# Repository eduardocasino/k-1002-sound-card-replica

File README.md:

# K-1002 8 bit audio Digital to Analog Converter replica

## About

This is a faithful replica of the K‑1002 8‑bit audio Digital‑to‑Analog Converter card for the KIM‑1, SYM‑1, and AIM‑65 computers, originally designed by MTU in the late ’70s.

I'm using the original K‑1002 documentation and high‑resolution photos from [Hans Otten's Retro Computing website](http://retro.hansotten.nl/).

### Important!

Although the card uses the familiar 44‑pin edge connector, it’s not a 1‑to‑1 match for the KIM‑1 application bus, so an adapter is required, as explained in the manual. I’ve also designed such an adapter, which you can find in the `adapter` folder.

## Building

There’s nothing particularly special about assembling the board. As with any other PCB, just start soldering components in order of height. All the ICs are socketed.

There’s a BOM spreadsheet in the `card/docs` folder, but there are a few things to keep in mind regarding some of the components:

* R1 to R13 are 51K resistors that need to be matched within 1%. You can either use modern metal‑film resistors with that tolerance or manually match carbon ones. I went with the latter to keep the look closer to the original.
Also, the documentation isn’t very clear about whether &plusmn;1% is actually enough or if it really means &plusmn;0.5% (so that all resistors fall within a 1% spread). I chose the latter interpretation as well.

* The 92PU01 and 92PU51 transistors are no longer available. The BD135‑10 and BD136‑10 are perfectly good functional replacements, but they use a different package and footprint, so you’ll need to bend the leads to fit them on the board.
 **NOTE**: They *must* be the "-10" variants!!

* The original potentiometer is no longer manufactured. A drop‑in replacement is the Piher PT15NH06 with the adjustment wheel. **NOTE**: Make sure you get the NH06 variant.

* The Keystone 571 RCA connector is no longer manufactured. Some suppliers may still have remaining stock, such as [TME](https://tme.eu) in Europe.

## KIM-1 Software and PC Utilities

I've only built it on a Debian Linux and on WSL with Ubuntu. I can't give support for other systems, sorry.

### Prerequisites

Any modern Linux distribution, tested on `Debian 12.6` and `Ubuntu 24.04`

Install the required packages:

```console
$ sudo apt update
$ sudo apt install build-essential cc65
```

### Build and usage

Just go to the `software` folder and run`make`:

```console
$ cd software
$ make
```

This will build the PC utilities and the KIM‑1 demo programs. The latter are generated in PAP format and are named with a numeric prefix that matches the file numbers in the K‑1002‑1L 8‑BIT Digital Music Software manual. Use them as instructed there.

Additionally, pcmplay.pap is a simple PCM player that plays a short sound snippet. Load it into your KIM-1 and run it at `$0200`.

The PC utilities are built into `software/utils/bin`:

* `wavegen` is a modern C version of the `kimfs` program. It generates a waveform table suitable for use with the MTU utilities from a very simle YAML description file.

* `notcmp` is the C version of the NOTRAN compiler. It accepts the same input files as its MTU counterpart and generates compatible object code for the NOTRAN interpreter.

* `notint` is a NOTRAN interpreter simulator that can either play a NOTRAN bytecode file through an ALSA device or generates WAV files to be played with any WAV player.

Run any of them without arguments to see the usage instructions.

## Licensing

This is a personal project that I am sharing in case it is of interest to any retrocomputing enthusiast and all the information in this repository is provided "as is", without warranty of any kind. I am not liable for any damages that may occur, whether it be to individuals, objects, KIM-1 computers, kittens or any other pets. **It should also be noted that everything in this repository is a work in progress and, although the board has been tested, may contain errors. Therefore, anyone who chooses to use it does so at their own risk**.

### Card

Th K-1002 replica is licensed under a [Creative Commons Attribution-NonCommercial 4.0 International License](http://creativecommons.org/licenses/by-nc/4.0/).

### Adapter

The adapter card is licensed under a [Creative Commons Attribution-ShareAlike 4.0 International License](http://creativecommons.org/licenses/by-sa/4.0/).

### MTU Software

Although it probably doesn’t matter much nowadays, since this software was written for a very obsolete and rare piece of hardware, the material is still copyrighted by MICRO TECHNOLOGY UNLIMITED, a company that is [still in business](http://www.mtu.com/catalog/index.php). I’m sharing it here solely to help anyone who owns a K‑1002 card.

### PC Utilities

All my code is licensed under the GNU General Public License, Version 3.

## Acknowledgements

* Hans Otten and his [Retro Computing blog](http://retro.hansotten.nl/). A lot of information and high resolution pictures of a K-1002

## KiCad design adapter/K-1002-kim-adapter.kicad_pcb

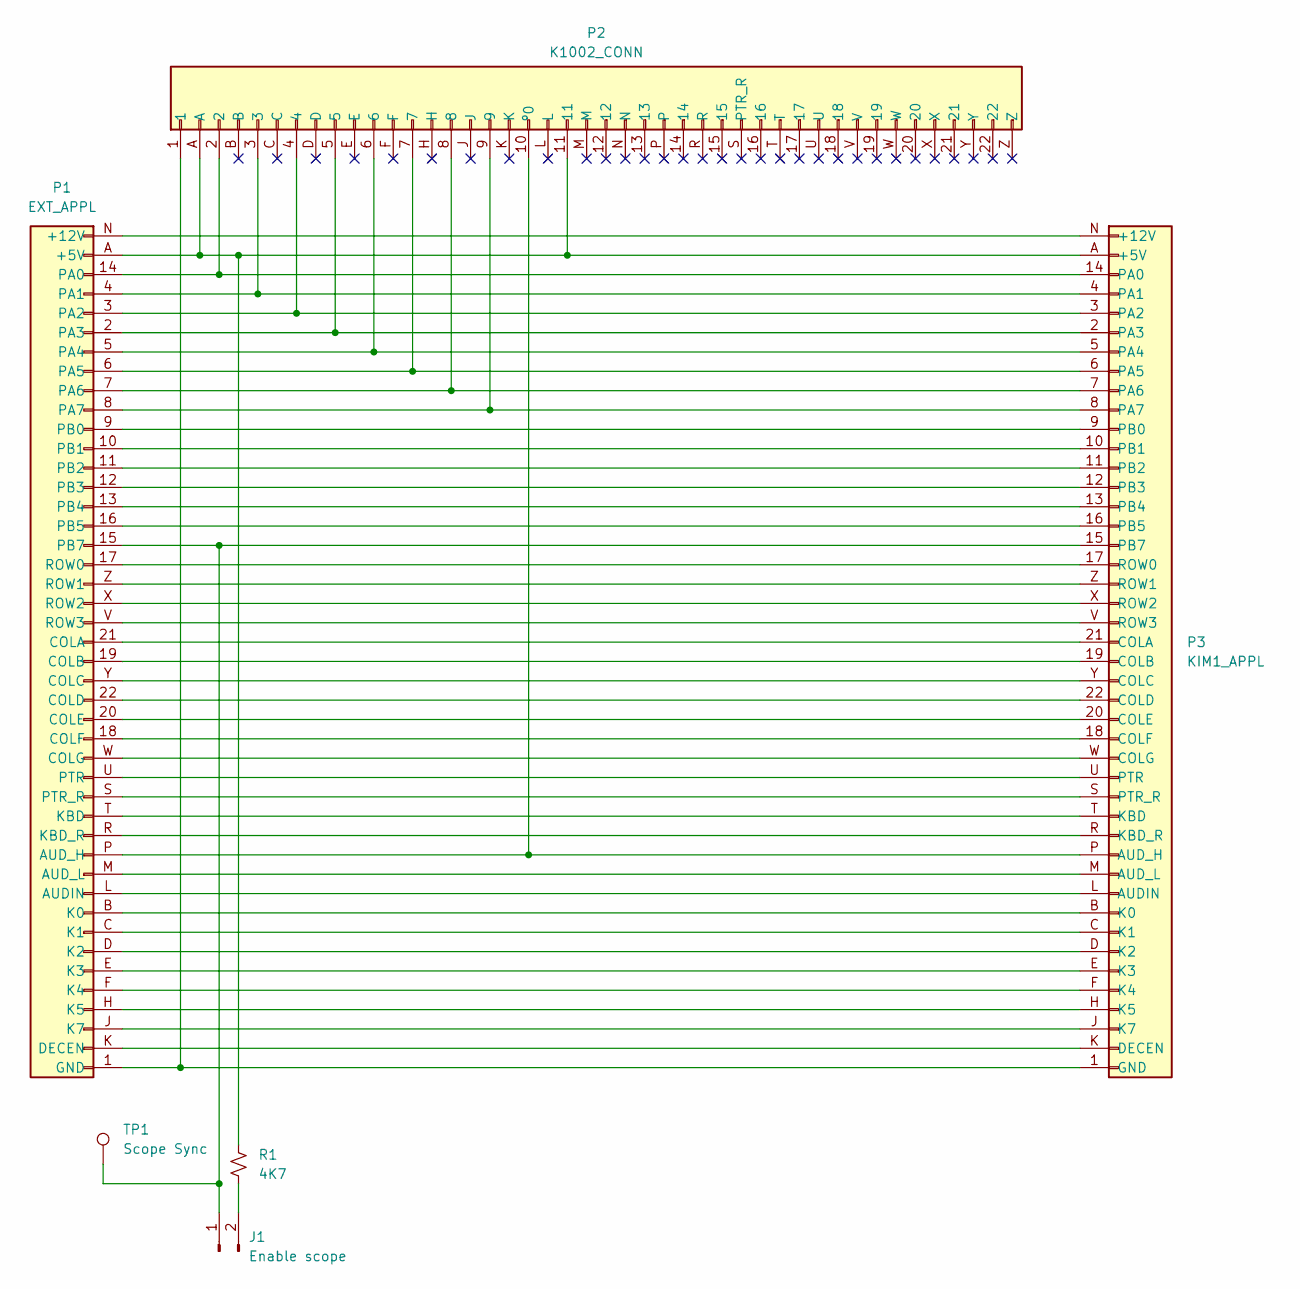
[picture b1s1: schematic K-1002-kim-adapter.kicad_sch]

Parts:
J1: Enable scope; PinHeader_1x02_P2.54mm_Vertical
P1: EXT_APPL; KIM_EDGE
P2: K1002_CONN; EDAC-3.96-2x22
P3: KIM1_APPL; APPL_CONN
R1: 4K7; R_Axial_DIN0207_L6.3mm_D2.5mm_P7.62mm_Horizontal
TP1: Scope Sync; TestPoint_3.0

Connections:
unnamed: J1.1, P1.15 (PB7), P3.15 (PB7), TP1.1
unnamed: J1.2, R1.2
unnamed: P1.A (+5V), P2.11, P2.A, P3.A (+5V), R1.1
unnamed: P1.N (+12V), P3.N (+12V)
unnamed: P1.L (AUDIN), P3.L (AUDIN)
unnamed: P1.P (AUD_H), P2.10 (º0), P3.P (AUD_H)
unnamed: P1.M (AUD_L), P3.M (AUD_L)
unnamed: P1.21 (COLA), P3.21 (COLA)
unnamed: P1.19 (COLB), P3.19 (COLB)
unnamed: P1.Y (COLC), P3.Y (COLC)
unnamed: P1.22 (COLD), P3.22 (COLD)
unnamed: P1.20 (COLE), P3.20 (COLE)
unnamed: P1.18 (COLF), P3.18 (COLF)
unnamed: P1.W (COLG), P3.W (COLG)
unnamed: P1.K (DECEN), P3.K (DECEN)
unnamed: P1.1 (GND), P2.1, P3.1 (GND)
unnamed: P1.B (K0), P3.B (K0)
unnamed: P1.C (K1), P3.C (K1)
unnamed: P1.D (K2), P3.D (K2)
unnamed: P1.E (K3), P3.E (K3)
unnamed: P1.F (K4), P3.F (K4)
unnamed: P1.H (K5), P3.H (K5)
unnamed: P1.J (K7), P3.J (K7)
unnamed: P1.T (KBD), P3.T (KBD)
unnamed: P1.R (KBD_R), P3.R (KBD_R)
unnamed: P1.14 (PA0), P2.2, P3.14 (PA0)
unnamed: P1.4 (PA1), P2.3, P3.4 (PA1)
unnamed: P1.3 (PA2), P2.4, P3.3 (PA2)
unnamed: P1.2 (PA3), P2.5, P3.2 (PA3)
unnamed: P1.5 (PA4), P2.6, P3.5 (PA4)
unnamed: P1.6 (PA5), P2.7, P3.6 (PA5)
unnamed: P1.7 (PA6), P2.8, P3.7 (PA6)
unnamed: P1.8 (PA7), P2.9, P3.8 (PA7)
unnamed: P1.9 (PB0), P3.9 (PB0)
unnamed: P1.10 (PB1), P3.10 (PB1)
unnamed: P1.11 (PB2), P3.11 (PB2)
unnamed: P1.12 (PB3), P3.12 (PB3)
unnamed: P1.13 (PB4), P3.13 (PB4)
unnamed: P1.16 (PB5), P3.16 (PB5)
unnamed: P1.U (PTR), P3.U (PTR)
unnamed: P1.S (PTR_R), P3.S (PTR_R)
unnamed: P1.17 (ROW0), P3.17 (ROW0)
unnamed: P1.Z (ROW1), P3.Z (ROW1)
unnamed: P1.X (ROW2), P3.X (ROW2)
unnamed: P1.V (ROW3), P3.V (ROW3)

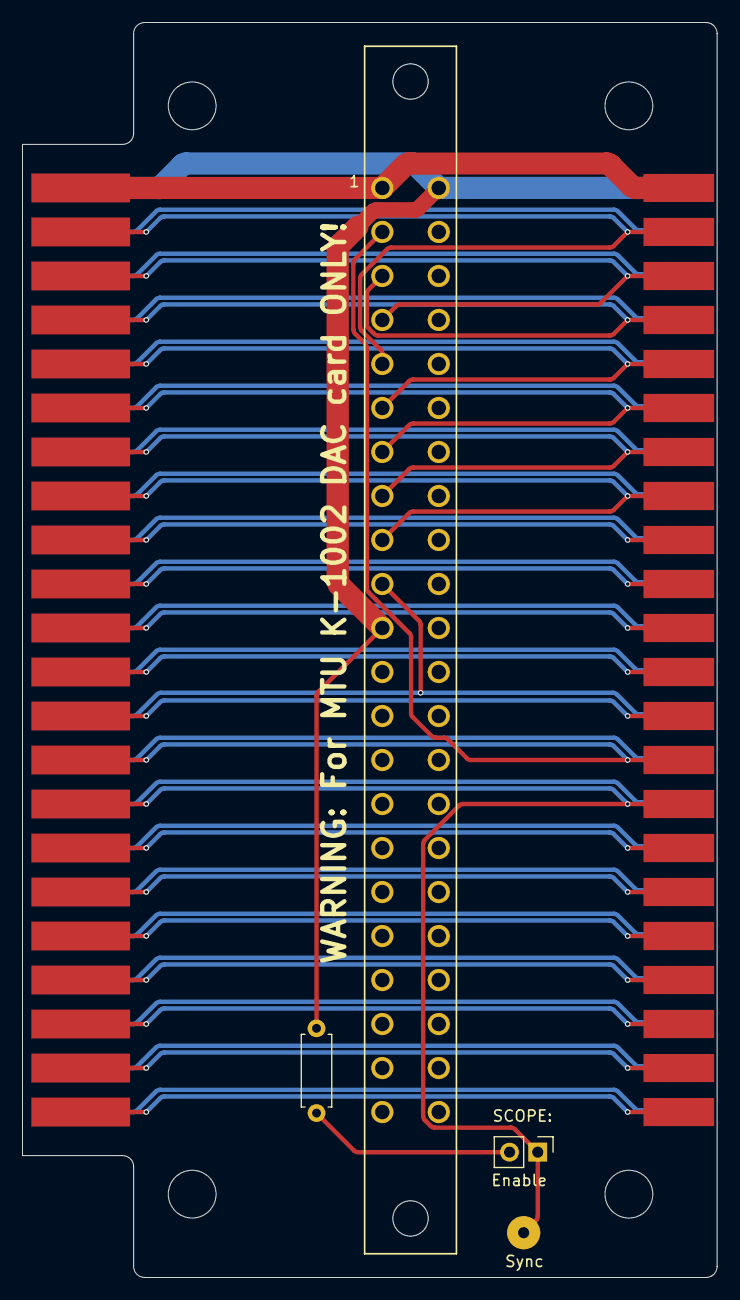
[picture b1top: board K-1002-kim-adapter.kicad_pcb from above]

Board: 2 copper layers, 62.5 x 112.9 mm, 10 parts (0 on the bottom side), 45 nets.

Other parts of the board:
M1, M1#2, M1#3, M2: MountingHole_4.3mm_M4

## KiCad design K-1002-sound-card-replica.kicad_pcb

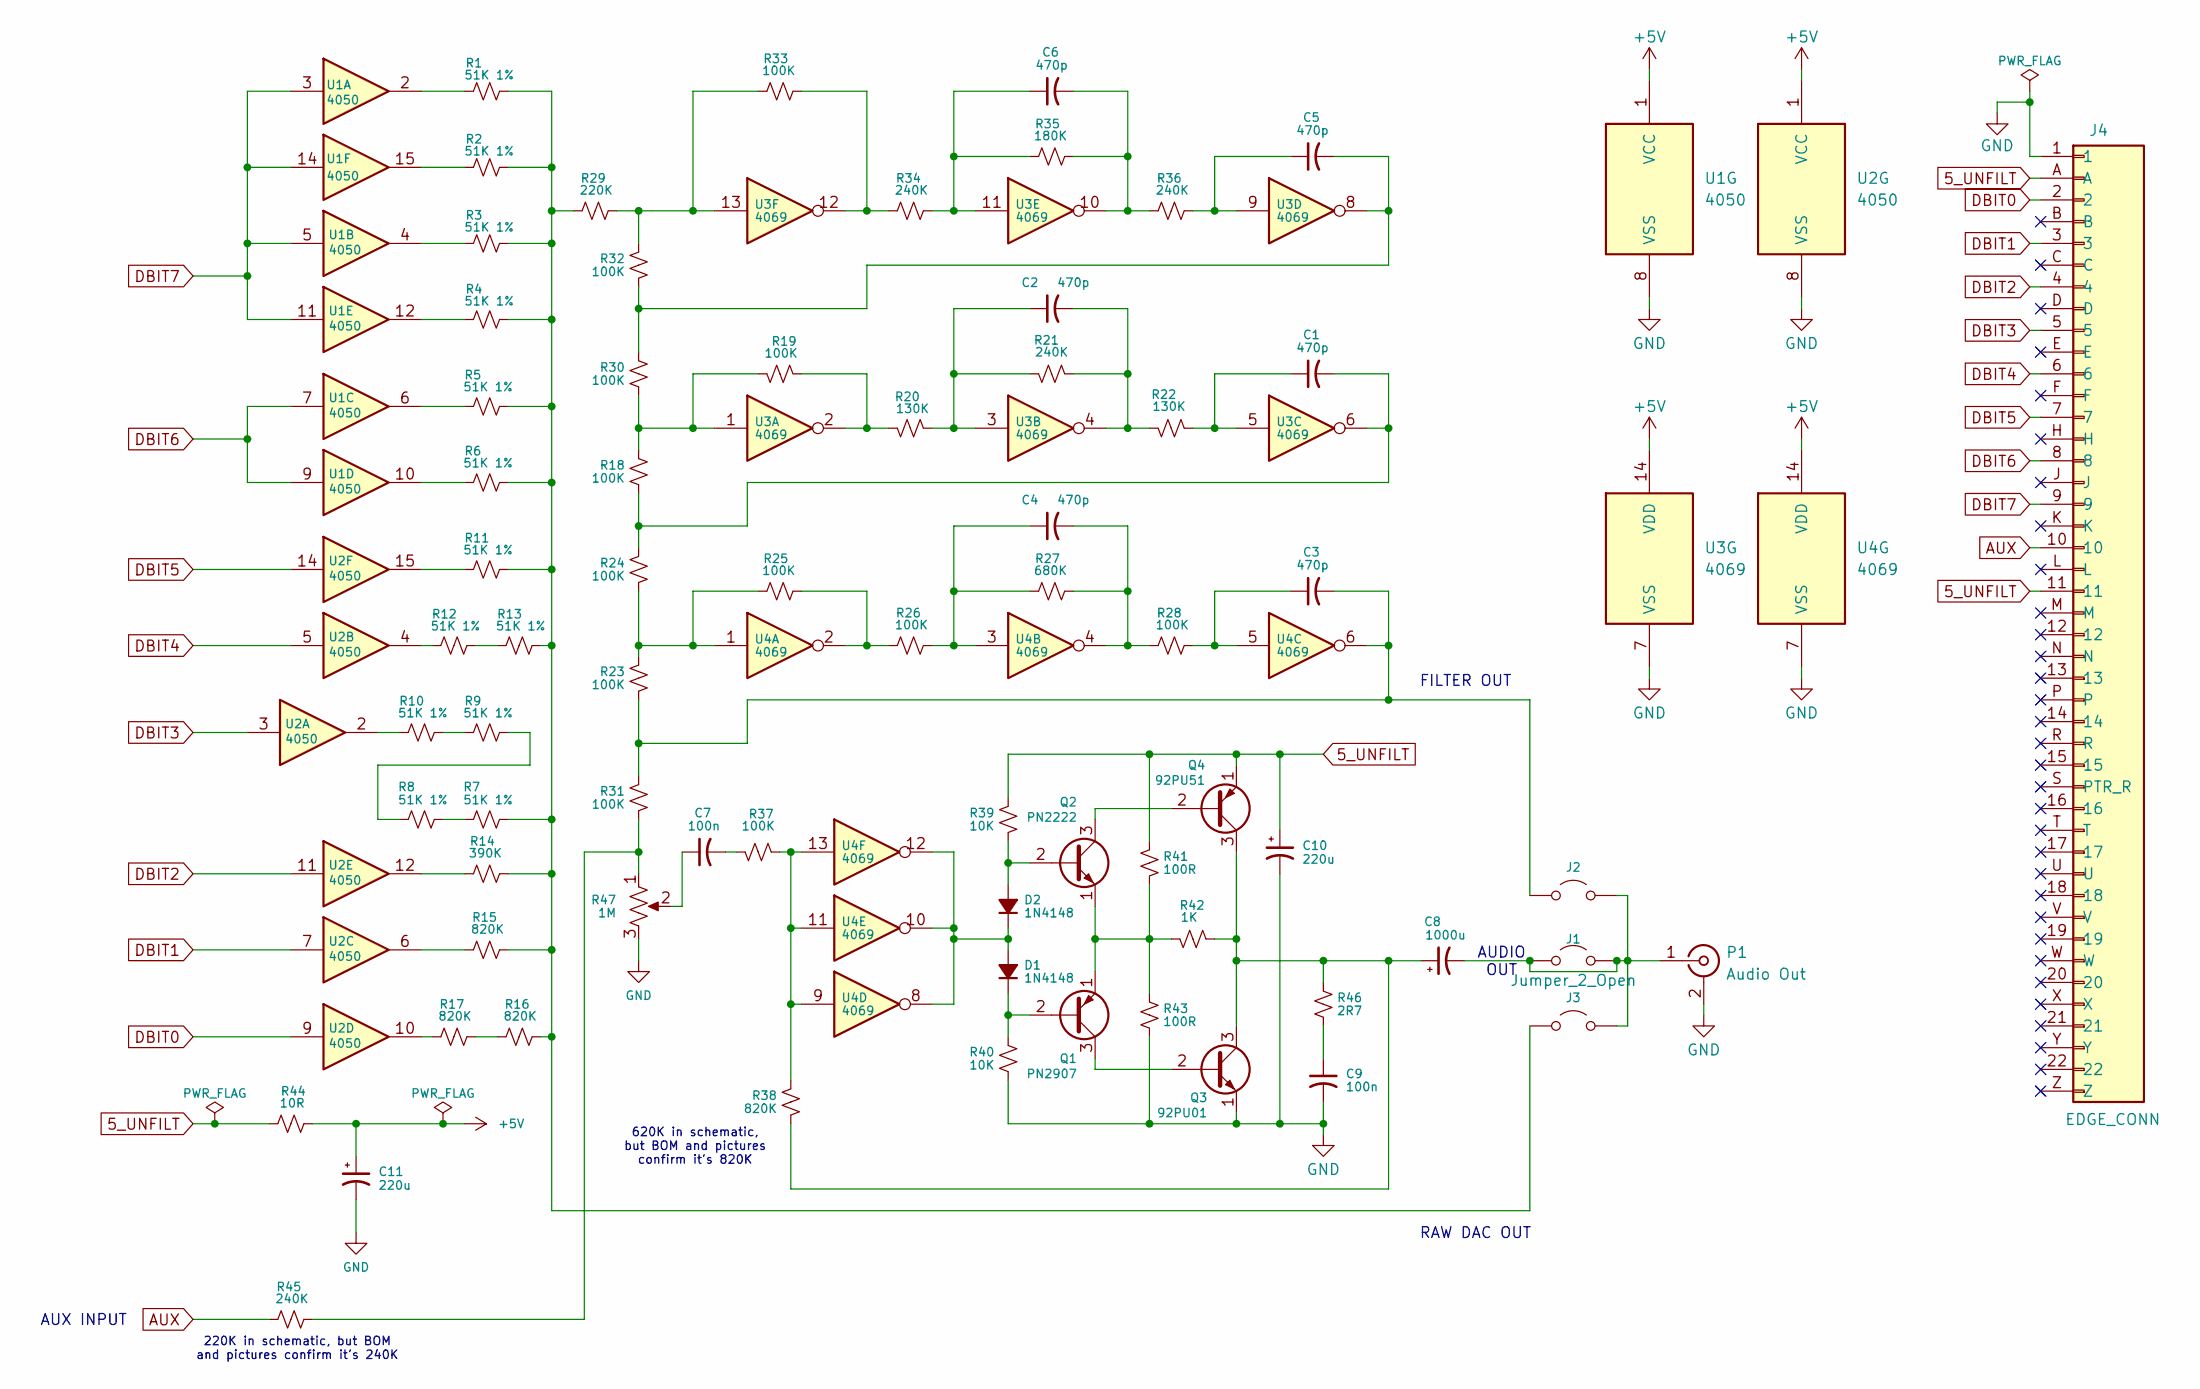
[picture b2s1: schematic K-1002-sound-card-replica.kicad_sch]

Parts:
C1, C2, C3, C4, C5, C6: 470p; C_Axial_L10.3mm_D4.7mm_P12.70mm_Horizontal
C7, C9: 100n; C_Disc_D7.0mm_W2.5mm_P6.35mm
C8: 1000u; C_Radial_D12.5mm_H20.0mm_P5.00mm
C10, C11: 220u; C_Radial_D10.0mm_H12.5mm_P5.00mm
D1, D2: 1N4148; D_DO-35_SOD27_P12.70mm_Horizontal
J1, J2, J3: Jumper_2_Open; Bridge_Open_P7.62mm
J4: EDGE_CONN
P1: Audio Out; Keystone_571_RCA
Q1: PN2907; TO-92-Custom
Q2: PN2222; TO-92-Custom
Q3: 92PU01; TO-92-Custom
Q4: 92PU51; TO-92-Custom
R1, R2, R3, R4, R5, R6, R7, R8, R9, R10, R11, R12, R13: 51K 1%; R_Axial_DIN0204_L3.6mm_D2.5mm_P12.70mm_Horizontal_51K
R14: 390K; R_Axial_DIN0204_L3.6mm_D2.5mm_P12.70mm_Horizontal_390K
R15, R16, R17, R38: 820K; R_Axial_DIN0204_L3.6mm_D2.5mm_P12.70mm_Horizontal_820K
R18, R19, R23, R24, R25, R26, R28, R30, R31, R32, R33, R37: 100K; R_Axial_DIN0204_L3.6mm_D2.5mm_P12.70mm_Horizontal_100K
R20, R22: 130K; R_Axial_DIN0204_L3.6mm_D2.5mm_P12.70mm_Horizontal_130K
R21, R34, R36, R45: 240K; R_Axial_DIN0204_L3.6mm_D2.5mm_P12.70mm_Horizontal_240K
R27: 680K; R_Axial_DIN0204_L3.6mm_D2.5mm_P12.70mm_Horizontal_680K
R29: 220K; R_Axial_DIN0204_L3.6mm_D2.5mm_P12.70mm_Horizontal_220K
R35: 180K; R_Axial_DIN0204_L3.6mm_D2.5mm_P12.70mm_Horizontal_180K
R39, R40: 10K; R_Axial_DIN0204_L3.6mm_D2.5mm_P12.70mm_Horizontal_10K
R41, R43: 100R; R_Axial_DIN0204_L3.6mm_D2.5mm_P12.70mm_Horizontal_100R
R42: 1K; R_Axial_DIN0204_L3.6mm_D2.5mm_P12.70mm_Horizontal_1K
R44: 10R; R_Axial_DIN0204_L3.6mm_D2.5mm_P12.70mm_Horizontal_10R
R46: 2R7; R_Axial_DIN0204_L3.6mm_D2.5mm_P12.70mm_Horizontal_2R7
R47: 1M; Piher_PT15-NH-06
U1, U2: 4050; DIP-16_W7.62mm_LongPads
U3, U4: 4069; DIP-14_W7.62mm_LongPads

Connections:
5_UNFILT: C10.1, J4.11, J4.A, Q4.1 (E), R39.1, R41.2, R44.1
+5V: C11.1, R44.2, U1.1 (VCC), U1.16, U2.1 (VCC), U2.16, U3.14 (VDD), U4.14 (VDD)
AUX: J4.10 (º0), R45.1
DBIT0: J4.2, U2.9
DBIT1: J4.3, U2.7
DBIT2: J4.4, U2.11
DBIT3: J4.5, U2.3
DBIT4: J4.6, U2.5
DBIT5: J4.7, U2.14
DBIT6: J4.8, U1.7, U1.9
DBIT7: J4.9, U1.3, U1.5, U1.11, U1.13, U1.14
GND: C9.2, C10.2, C11.2, J4.1, P1.2 (Ext), Q3.1 (E), R40.1, R43.2, R47.3, U1.8 (VSS), U2.8 (VSS), U3.7 (VSS), U4.7 (VSS)
unnamed: C1.1, R22.1, U3.5
unnamed: C1.2, R18.1, R24.1, U3.6
unnamed: C2.1, R20.1, R21.2, U3.3
unnamed: C2.2, R21.1, R22.2, U3.4
unnamed: C3.1, R28.2, U4.5
unnamed: C4.1, R26.2, R27.1, U4.3
unnamed: C4.2, R27.2, R28.1, U4.4
unnamed: C5.1, R36.2, U3.9
unnamed: C5.2, R30.2, R32.2, U3.8
unnamed: C6.1, R34.2, R35.1, U3.11
unnamed: C6.2, R35.2, R36.1, U3.10
unnamed: C7.1, R47.2
unnamed: C7.2, R37.2
unnamed: C9.1, R46.2
unnamed: D1.2 (A), D2.1 (K), U4.8, U4.10, U4.12
unnamed: D1.1 (K), Q1.2 (B), R40.2
unnamed: D2.2 (A), Q2.2 (B), R39.2
unnamed: C8.2, J1.1 (A), J1.2 (B), J2.2 (B), J3.2 (B), P1.1 (In)
unnamed: C3.2, J2.1 (A), R23.2, R31.1, U4.6
unnamed: J3.1 (A), R1.2, R2.2, R3.2, R4.2, R5.2, R6.2, R7.2, R11.2, R13.2, R14.2, R15.2, R16.2, R29.1
unnamed: Q1.3 (C), Q3.2 (B)
unnamed: Q1.1 (E), Q2.1 (E), R41.1, R42.2, R43.1
unnamed: Q2.3 (C), Q4.2 (B)
unnamed: C8.1, Q3.3 (C), Q4.3 (C), R38.2, R42.1, R46.1
unnamed: R1.1, U1.2
unnamed: R2.1, U1.15
unnamed: R3.1, U1.4
unnamed: R4.1, U1.12
unnamed: R5.1, U1.6
unnamed: R6.1, U1.10
unnamed: R7.1, R8.2
unnamed: R8.1, R9.2
unnamed: R10.1, U2.2
unnamed: R9.1, R10.2
unnamed: R11.1, U2.15
unnamed: R12.1, U2.4, U2.13
unnamed: R12.2, R13.1
unnamed: R14.1, U2.12
unnamed: R15.1, U2.6
unnamed: R16.1, R17.2
unnamed: R17.1, U2.10
unnamed: R18.2, R19.2, R30.1, U3.1
unnamed: R19.1, R20.2, U3.2
unnamed: R23.1, R24.2, R25.1, U4.1
unnamed: R25.2, R26.1, U4.2
unnamed: R29.2, R32.1, R33.1, U3.13
unnamed: R31.2, R45.2, R47.1
unnamed: R33.2, R34.1, U3.12
unnamed: R37.1, R38.1, U4.9, U4.11, U4.13

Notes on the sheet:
220K in schematic, but BOM and pictures confirm it's 240K
AUDIO OUT
RAW DAC OUT
620K in schematic, but BOM and pictures confirm it's 820K
AUX INPUT
FILTER OUT

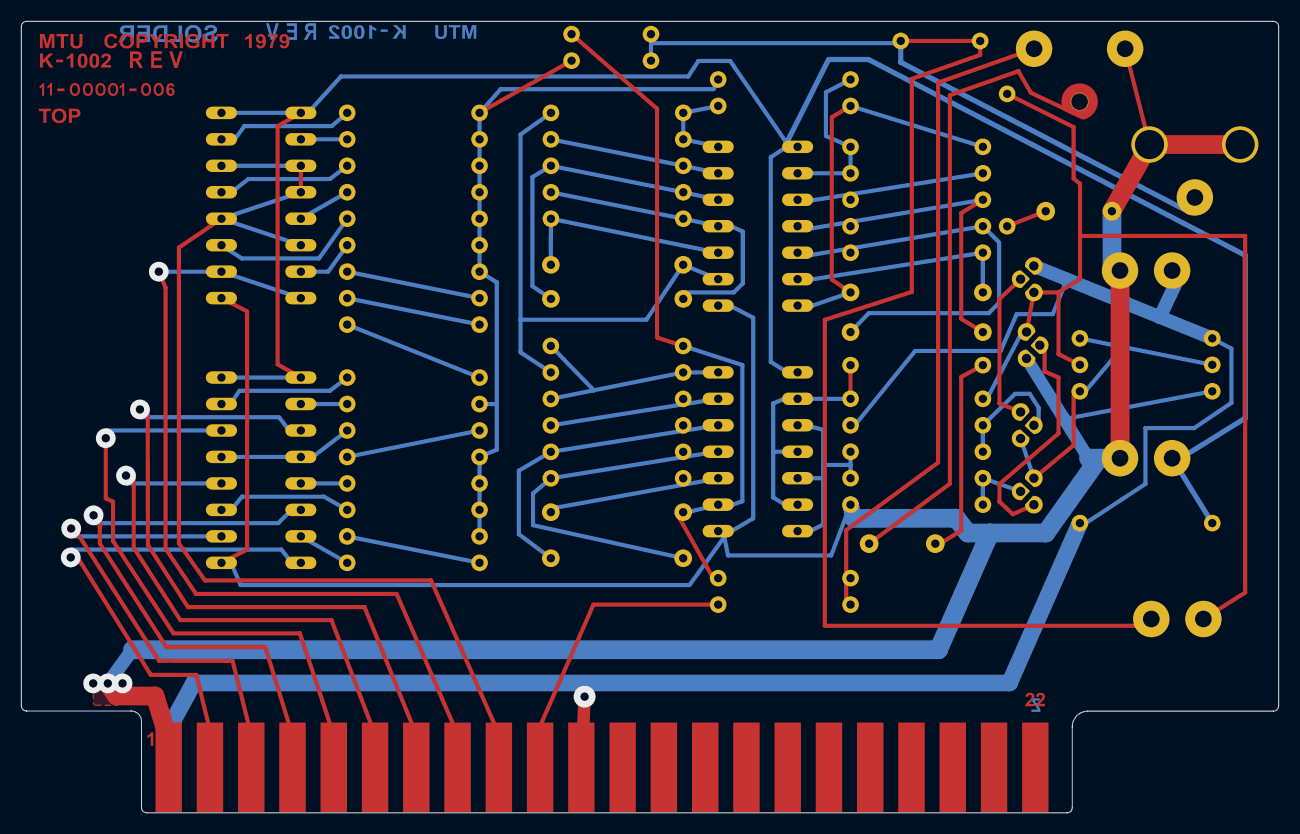
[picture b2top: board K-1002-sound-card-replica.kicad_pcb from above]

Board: 2 copper layers, 120.7 x 76.0 mm, 73 parts (0 on the bottom side), 61 nets.

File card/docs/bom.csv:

Reference,Qty,Type,Value,Notes,
"C1,C2,C3,C4,C5,C6",6,polystyrene,470p,,
"C7,C9",2,"ceramic, 12V, Z5U",100n,,
C8,1,"electrolytic, 10V",1000u,,
"C10,C11",2,"electrolytic, 6V",220u,,
"D1,D2",2,,1N4148,,
P1,1,RCA Keystone 571,,,
Q1,1,,PN2907,,
Q2,1,,PN2222,,
Q3,1,,92PU01,Alternative:,BD135-10
Q4,1,,92PU51,Alternative:,BD136-10
"R1,R2,R3,R4,R5,R6,R7,R8,R9,R10,R11,R12,R13",13,"Carbon, 0.25W",51K,Matched to 1%,
R14,1,"Carbon, 0.25W",390K,,
"R15,R16,R17,R38",4,"Carbon, 0.25W",820K,,
"R18,R19,R23,R24,R25,R26,R28,R30,R31,R32,R33,R37",12,"Carbon, 0.25W",100K,,
"R20,R22",2,"Carbon, 0.25W",130K,,
"R21,R34,R36,R45",4,"Carbon, 0.25W",240K,,
R27,1,"Carbon, 0.25W",680K,,
R29,1,"Carbon, 0.25W",220K,,
R35,1,"Carbon, 0.25W",180K,,
"R39,R40",2,"Carbon, 0.25W",10K,,
"R41,R43",2,"Carbon, 0.25W",100R,,
R42,1,"Carbon, 0.25W",1K,,
R44,1,"Carbon, 0.25W",10R,,
R46,1,"Carbon, 0.25W",2R7,,
R47,1,Piher PT15NH06,1M,Alternative:,16PMI-1MSR PASSIVES
"U1,U2",2,,CD4050,,
"U3,U4",2,,CD4069,,

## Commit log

2025-12-20 First hardware commit
2025-12-21 Move card design to its own directory
2025-12-21 First commit of the adapter
2026-01-03 Add software and utilities
2026-01-03 Add README file
2026-01-04 Typo in README.md, missing a '1'
2026-01-05 Add note about the Keystone 571 RCA connector
2026-01-07 Update adapter renders

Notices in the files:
README.md:
CC BY-NC 4.0
CC BY-SA 4.0
adapter/K-1002-kim-adapter.kicad_pcb:
CC-BY-SA
